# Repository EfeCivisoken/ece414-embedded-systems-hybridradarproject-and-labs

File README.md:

# ECE 414 – Embedded Systems & Hybrid Radar Project

This repository contains the complete set of lab assignments and the final project for **ECE 414 – Embedded Systems**, including all supporting code, reports, and documentation.

---

## ⚠️ Important Note

This repository is a **clean, standalone copy** created for archival and submission purposes.

The original development repository — including full commit history and iterative work — is available here:

🔗 **https://github.com/JackE772/ece414-civisoken-ewing**

---

## 📁 Repository Structure

├── lab1/ # Introductory embedded systems lab
├── lab2/ # Peripheral interfacing and MCU fundamentals
├── lab03_v4/ # Advanced lab iteration
├── lab04/ # Timing, interrupts, and peripherals
├── lab05_v1 # Final lab iteration
├── Lab03_Pong/ # Pong-based embedded systems project
├── final-project/ # Hybrid Ultrasonic–Radar Final Project
│
├── ECE414 Hybrid Ultrasonic Radar System Report.pdf
├── Grading Justification.pdf
└── README.md

---

## 📌 Final Project Overview

**Title:** Hybrid Ultrasonic–Radar Embedded System  
**Platform:** Microcontroller-based (C/C++, bare-metal with peripheral drivers)

### Focus Areas
- Sensor fusion (ultrasonic + radar)
- Real-time signal acquisition and processing
- Hardware–software integration
- Embedded timing, interrupts, and low-level control
- System-level validation and performance analysis

The final project demonstrates the integration of multiple sensing modalities into a cohesive embedded system with real-time constraints, supported by comprehensive documentation and justification.

---

## 🧠 Purpose of This Repository

This repository exists to:

- Provide a clean, submission-ready version of the project  
- Separate finalized coursework from active development history  
- Present a clear and structured layout for academic evaluation  

---

## 📎 Original Development Repository

🔗 **https://github.com/JackE772/ece414-civisoken-ewing**

*(Contains full commit history, experimental branches, and iterative development work.)*

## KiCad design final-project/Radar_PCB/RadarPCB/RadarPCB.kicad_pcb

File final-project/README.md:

# Hybrid Ultrasonic–Doppler Radar System

ECE 414 – Embedded Systems Final Project  
Platform: Raspberry Pi Pico (RP2040)
Efe Civisoken , Jack Ewing
---

## What This Project Does

This project runs a hybrid sensing system on a Raspberry Pi Pico that:
- Measures distance using ultrasonic time-of-flight
- Detects motion using a microwave Doppler sensor
- Sweeps sensors using servo motors
- Displays a radar-style visualization on a TFT screen
- Streams telemetry over USB serial

---

## What You Need

## Hardware
- Raspberry Pi Pico (RP2040)
- 2× HC-SR04 ultrasonic sensors
- 2× HB100 Doppler radar modules
- 2× hobby servo motors
- SPI TFT display (ILI934x family)
- External 5 V USB power
- Breadboards and jumper wires

## Hardware Setup

All wiring, power connections, and signal routing are documented in the **electrical schematics provided in the `Radar_PCB/` folder**.  
These schematics were created using **KiCad** and serve as the authoritative reference for hardware setup.

To assemble the system:
- Follow the KiCad schematic files in `Radar_PCB/` for all GPIO, power, and ground connections
- Ensure the Doppler radar modules and analog conditioning circuitry are physically separated from high-current digital components (servos, display, Pico) to minimize noise
- Use a stable 5 V supply capable of sourcing sufficient current for the servos

No additional hardware configuration is required beyond what is shown in the schematics.

---

### Software
- Raspberry Pi Pico SDK
- CMake (v3.13+)
- GCC ARM Embedded Toolchain
- Make

Make sure the Pico SDK is cloned locally.

---

## Build and Flash Instructions

From the project directory, run:

```bash
rm -rf build
mkdir build
cd build
cmake .. -DPICO_SDK_PATH=../pico-sdk -DPICO_BOARD=pico2
make -j$(nproc)

```

## This creates a .uf2 firmware file in the build directory.

Flash to the Pico
Hold the BOOTSEL button on the Pico

Plug the Pico into your computer via USB

Drag and drop the .uf2 file onto the Pico drive

## Running the System
After flashing:

Servos begin sweeping automatically

Ultrasonic distance measurements run at each angle

Doppler motion detection runs continuously

A radar-style display appears on the TFT

Telemetry is sent over USB serial

View Serial Output
Use any serial terminal:

Baud rate: 115200

Output includes angle, distance, motion flag, and RMS values

## Notes
Build artifacts are ignored by .gitignore

Display and touchscreen drivers are reused from earlier ECE 414 labs

Doppler analog circuitry should be physically separated from digital components for best results

## Demo
A working demo video is available here:

<https://drive.google.com/file/d/15QqWR9_1v-_UHlbc8YgBszJ1aU8pvBwp/view?usp=sharing>

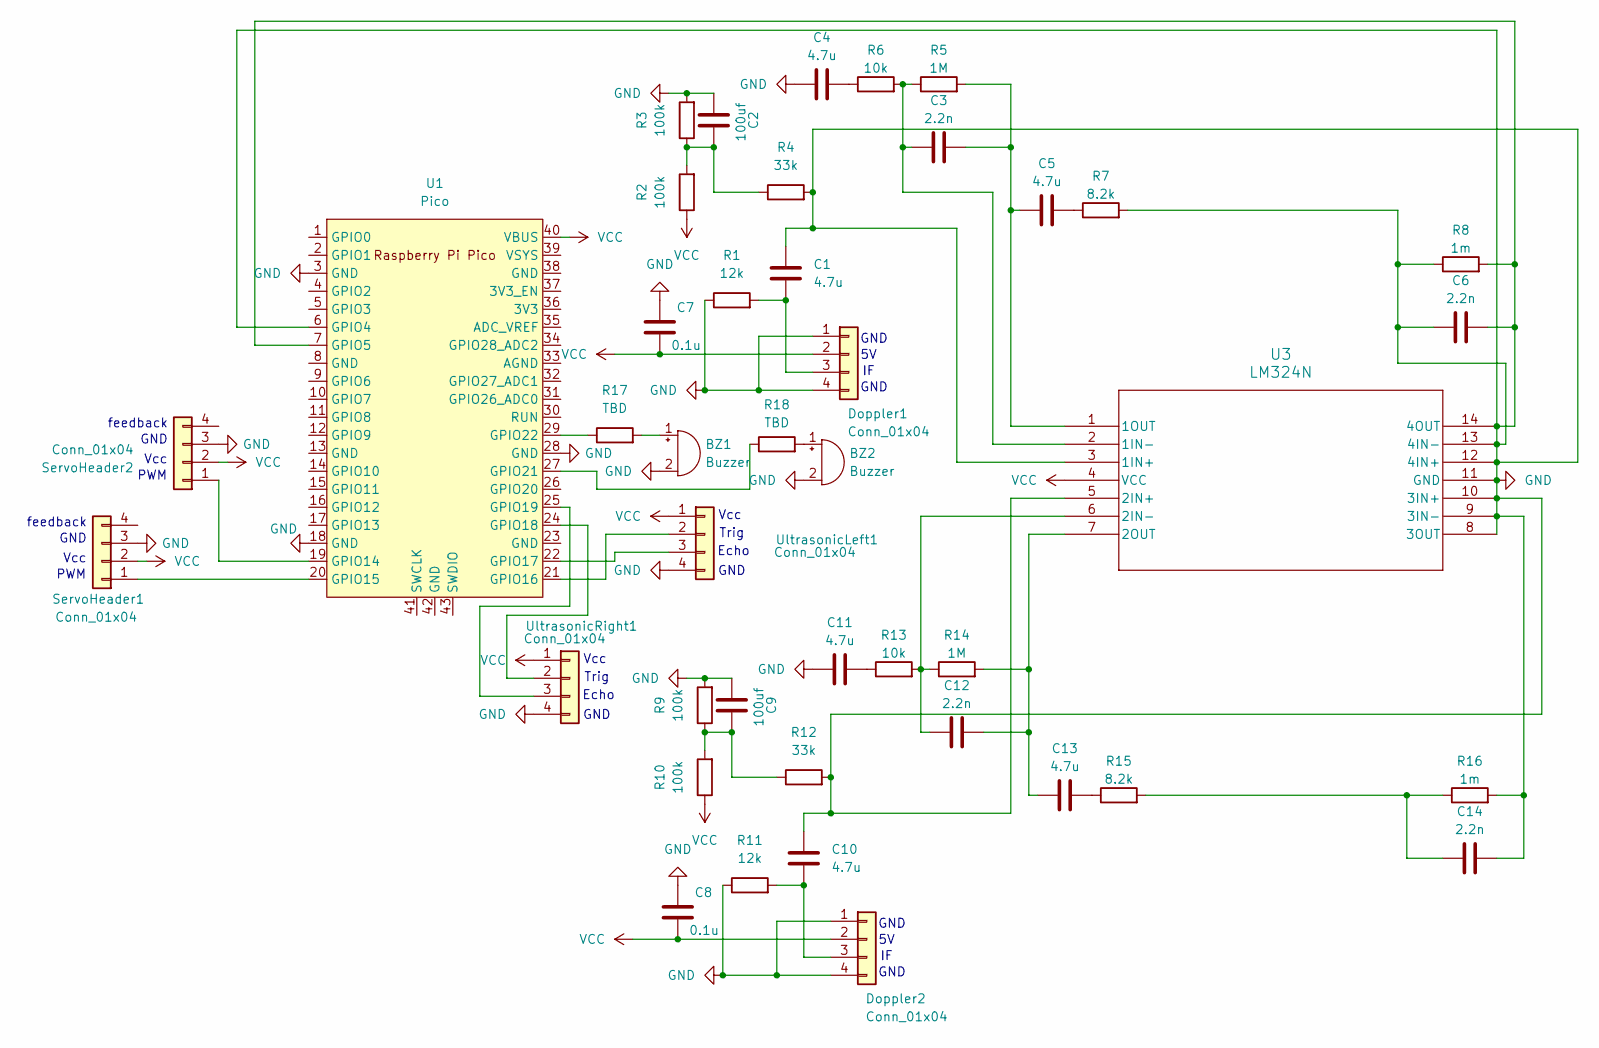
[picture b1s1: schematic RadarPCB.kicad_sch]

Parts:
BZ1, BZ2: Buzzer; COM07950
C1, C4, C5, C10, C11, C13: 4.7u; CP_Radial_D8.0mm_P3.80mm
C2, C9: 100uf; CP_Radial_D8.0mm_P3.80mm
C3, C6, C12, C14: 2.2n; CP_Radial_D8.0mm_P3.80mm
C7, C8: 0.1u; CP_Radial_D8.0mm_P3.80mm
Doppler1, Doppler2: Conn_01x04; HB100
R1, R11: 12k; R_Axial_DIN0204_L3.6mm_D1.6mm_P7.62mm_Horizontal
R2, R3, R9, R10: 100k; R_Axial_DIN0204_L3.6mm_D1.6mm_P7.62mm_Horizontal
R4, R12: 33k; R_Axial_DIN0204_L3.6mm_D1.6mm_P7.62mm_Horizontal
R5, R14: 1M; R_Axial_DIN0204_L3.6mm_D1.6mm_P7.62mm_Horizontal
R6, R13: 10k; R_Axial_DIN0204_L3.6mm_D1.6mm_P7.62mm_Horizontal
R7, R15: 8.2k; R_Axial_DIN0204_L3.6mm_D1.6mm_P7.62mm_Horizontal
R8, R16: 1m; R_Axial_DIN0204_L3.6mm_D1.6mm_P7.62mm_Horizontal
R17, R18: TBD; R_Axial_DIN0204_L3.6mm_D1.6mm_P7.62mm_Horizontal
ServoHeader1, ServoHeader2: Conn_01x04; PinSocket_1x04_P2.54mm_Vertical
U1: Pico; RaspberryPi_Pico_Common_Unspecified
U3: LM324N; N14
UltrasonicLeft1: Conn_01x04; PinSocket_1x04_P2.54mm_Vertical
UltrasonicRight1: Conn_01x04; PinSocket_1x04_P2.54mm_Vertical

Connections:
GND: BZ1.2 (-), BZ2.2 (-), C1.1, C2.2, C4.2, C6.1, C6.2, C7.1, C8.1, C9.2, C10.1, C11.2, C14.1, Doppler1.1, Doppler1.4, Doppler2.1, Doppler2.4, R1.1, R3.2, R4.2, R7.2, R8.1, R8.2, R9.2, R11.1, R12.2, R16.2, ServoHeader1.3, ServoHeader2.3, U1.3 (GND), U1.6 (GPIO4), U1.7 (GPIO5), U1.18 (GND), U1.28 (GND), U3.3 (1IN+), U3.5 (2IN+), U3.8 (3OUT), U3.9 (3IN-), U3.10 (3IN+), U3.11 (GND), U3.12 (4IN+), U3.13 (4IN-), U3.14 (4OUT), UltrasonicLeft1.4, UltrasonicRight1.4
unnamed: BZ1.1 (+), R17.2
unnamed: BZ2.1 (+), R18.2
unnamed: C2.1, R2.2, R3.1, R4.1
unnamed: C4.1, R6.1
unnamed: C5.1, R7.1
unnamed: C9.1, R9.1, R10.2, R12.1
unnamed: C11.1, R13.1
unnamed: C13.1, R15.1
unnamed: C14.2, R15.2, R16.1
unnamed: C1.2, Doppler1.3, R1.2
unnamed: C10.2, Doppler2.3, R11.2
unnamed: ServoHeader1.1, U1.20 (GPIO15)
unnamed: ServoHeader2.1, U1.19 (GPIO14)
unnamed 15: U1.21 (GPIO16), UltrasonicLeft1.2; also elsewhere on the board
unnamed 16: U1.22 (GPIO17), UltrasonicLeft1.3; also elsewhere on the board
unnamed: U1.24 (GPIO18), UltrasonicRight1.2
unnamed: U1.25 (GPIO19), UltrasonicRight1.3
unnamed: R18.1, U1.27 (GPIO21)
unnamed: R17.1, U1.29 (GPIO22)
unnamed: C3.2, R5.1, R6.2, U3.2 (1IN-)
unnamed: C3.1, C5.2, R5.2, U3.1 (1OUT)
unnamed: C12.2, R13.2, R14.1, U3.6 (2IN-)
unnamed: C12.1, C13.2, R14.2, U3.7 (2OUT)
VCC: C7.2, C8.2, Doppler1.2, Doppler2.2, R2.1, R10.1, ServoHeader1.2, ServoHeader2.2, U1.40 (VBUS), U3.4 (VCC), UltrasonicLeft1.1, UltrasonicRight1.1; also elsewhere on the board

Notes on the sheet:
GND
Vcc
Echo
feedback
PWM
Trig

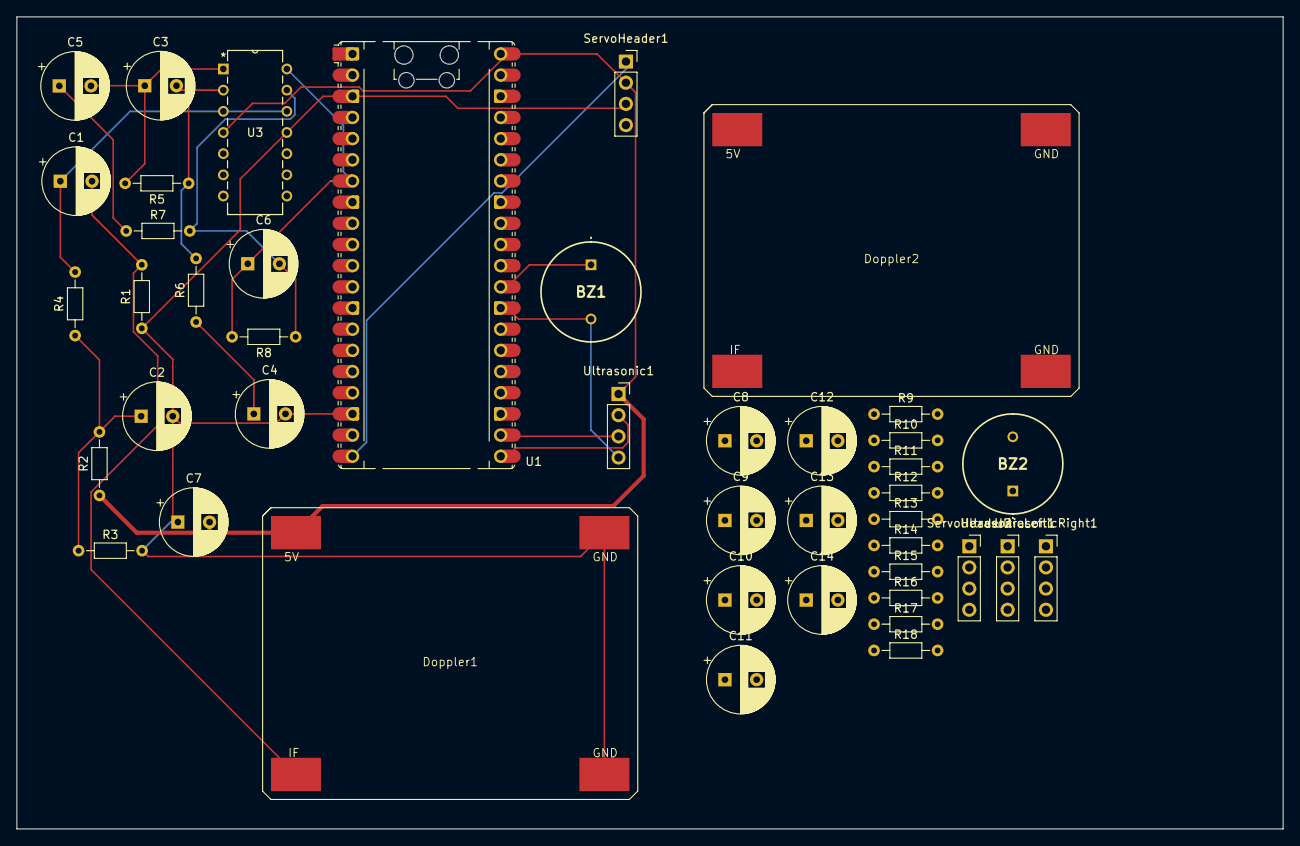
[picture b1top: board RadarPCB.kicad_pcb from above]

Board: 2 copper layers, 151.9 x 97.4 mm, 43 parts (0 on the bottom side), 25 nets.

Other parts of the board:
Ultrasonic1: Conn_01x04; PinSocket_1x04_P2.54mm_Vertical

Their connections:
unnamed 15: Ultrasonic1.2; also elsewhere on the board
unnamed 16: Ultrasonic1.3; also elsewhere on the board
VCC: Ultrasonic1.1; also elsewhere on the board

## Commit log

2026-01-02 Final Project's Report and Grade Justification attached.
2026-01-02 Final version with final project, report/justification, and labs
2026-01-02 README
2026-01-02 README fix
